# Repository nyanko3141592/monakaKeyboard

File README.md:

# monakaKeyboard

monakaKeyboard は、自作キーボードのプロジェクトです。このリポジトリには、キーボードの設計ファイル、ファームウェア、キーキャップデザイン、ケースの 3D モデルなどが含まれています。

## プロジェクト構成

```
.
├── 3DModel
│   ├── Case
│   │   ├── bottomboard.stl
│   │   └── topboard.stl
│   └── keycap
│       ├── alphabet_keycap.stl
│       └── symbol_keycap.stl
├── 3x7
├── README.md
└── choco002
    ├── keyboard.json
    ├── keymaps
    │   └── default
    │       └── keymap.c
    └── readme.md
```

### 3DModel

- `Case/`  
  ケースの 3D モデルが含まれています。

  - `bottomboard.stl` - 底板の 3D モデル
  - `topboard.stl` - 上部パネルの 3D モデル

- `keycap/`  
  キーキャップの 3D モデルが含まれています。
  - `alphabet_keycap.stl` - アルファベットキー用キーキャップ
  - `symbol_keycap.stl` - シンボルキー用キーキャップ

### 3x7

3x7 キー配列の設計データが含まれています。
3x7/DisliKey.kicad_pro から kicad で開いて Gerber ファイルを発注することができます。

### choco002

QMK ファームウェアの設定ファイルが含まれています。

- `keyboard.json`  
  キーボードの設定ファイルです。

- `keymaps/`  
  キーマップの定義が含まれています。
  - `default/keymap.c` - デフォルトのキーマップ定義

## 使い方

### 3D モデルの印刷

`3DModel`ディレクトリ内の STL ファイルを 3D プリンターで印刷してください。ケースとキーキャップを含めた全ての部品を印刷することで、物理的なキーボードを組み立てることができます。

### QMK ファームウェアの設定

`choco002`ディレクトリ内のファイルを使用して、QMK ファームウェアをビルドおよびフラッシュします。キーマップはデフォルト設定で使用できますが、`keymap.c`ファイルを編集することでカスタマイズが可能です。

1. QMK CLI をインストールしていない場合は[こちら](https://docs.qmk.fm/#/ja/getting_started_build_tools)からインストールしてください。
2. `choco002`ディレクトリに移動し、次のコマンドを実行します。

   ```
   qmk compile -kb choco002 -km default
   qmk flash -kb choco002 -km default
   ```

## ライセンス

このプロジェクトは、商用利用を除く目的での使用、改変、および出力を許可します。

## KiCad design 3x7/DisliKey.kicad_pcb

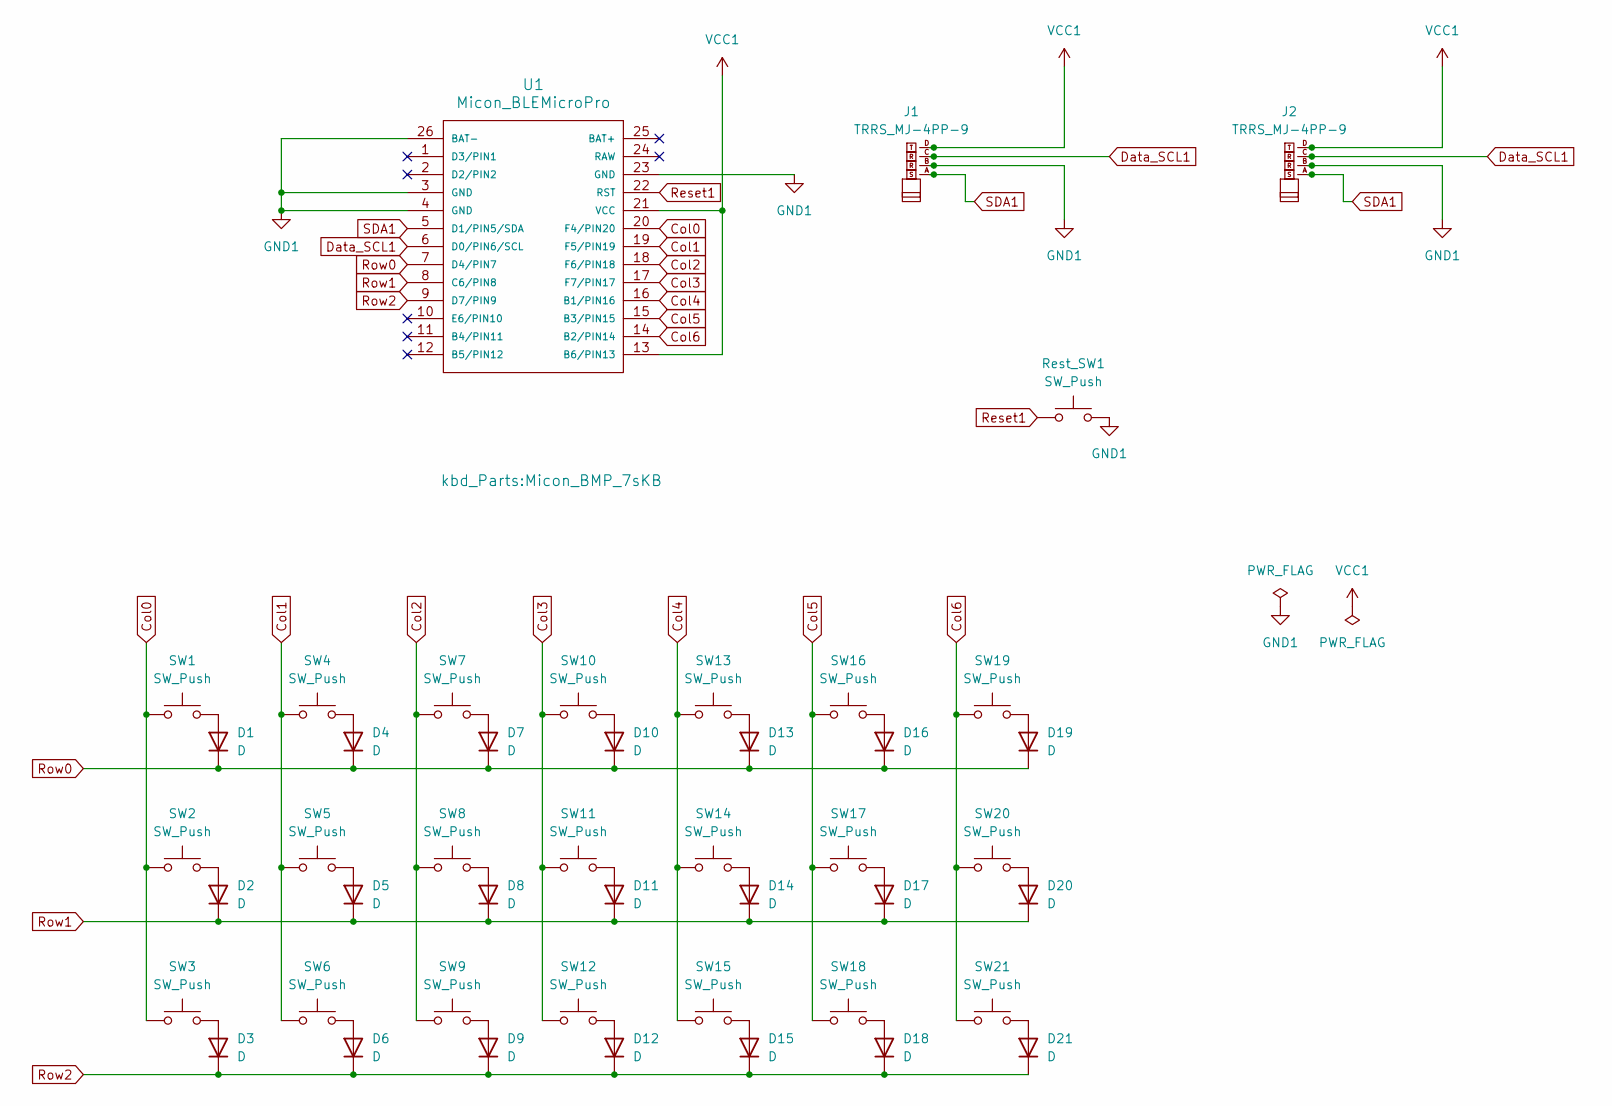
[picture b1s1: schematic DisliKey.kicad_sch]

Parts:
D1, D2, D3, D4, D5, D6, D7, D8, D9, D10, D11, D12, D13, D14, D15, D16, D17, D18, D19, D20, D21: D; Diode_TH
J1, J2: TRRS_MJ-4PP-9
Rest_SW1: SW_Push; ResetSW
SW1, SW2, SW3, SW4, SW5, SW6, SW7, SW8, SW9, SW10, SW11, SW12, SW13, SW14, SW15, SW16, SW17, SW18, SW19, SW20, SW21: SW_Push; CherryMX_Solder_1u
U1: Micon_BLEMicroPro; Micon_BMP_7sKB

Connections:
Col0: SW1.1, SW2.1, SW3.1, U1.20 (F4/PIN20)
Col1: SW4.1, SW5.1, SW6.1, U1.19 (F5/PIN19)
Col2: SW7.1, SW8.1, SW9.1, U1.18 (F6/PIN18)
Col3: SW10.1, SW11.1, SW12.1, U1.17 (F7/PIN17)
Col4: SW13.1, SW14.1, SW15.1, U1.16 (B1/PIN16)
Col5: SW16.1, SW17.1, SW18.1, U1.15 (B3/PIN15)
Col6: SW19.1, SW20.1, SW21.1, U1.14 (B2/PIN14)
Data_SCL1: J1.C, J2.C, U1.6 (D0/PIN6/SCL)
GND1: J1.B, J2.B, Rest_SW1.2, U1.3 (GND), U1.4 (GND), U1.23 (GND), U1.26 (BAT-)
unnamed: D1.2 (A), SW1.2
unnamed: D2.2 (A), SW2.2
unnamed: D3.2 (A), SW3.2
unnamed: D4.2 (A), SW4.2
unnamed: D5.2 (A), SW5.2
unnamed: D6.2 (A), SW6.2
unnamed: D7.2 (A), SW7.2
unnamed: D8.2 (A), SW8.2
unnamed: D9.2 (A), SW9.2
unnamed: D10.2 (A), SW10.2
unnamed: D11.2 (A), SW11.2
unnamed: D12.2 (A), SW12.2
unnamed: D13.2 (A), SW13.2
unnamed: D14.2 (A), SW14.2
unnamed: D15.2 (A), SW15.2
unnamed: D16.2 (A), SW16.2
unnamed: D17.2 (A), SW17.2
unnamed: D18.2 (A), SW18.2
unnamed: D19.2 (A), SW19.2
unnamed: D20.2 (A), SW20.2
unnamed: D21.2 (A), SW21.2
Reset1: Rest_SW1.1, U1.22 (RST)
Row0: D1.1 (K), D4.1 (K), D7.1 (K), D10.1 (K), D13.1 (K), D16.1 (K), D19.1 (K), U1.7 (D4/PIN7)
Row1: D2.1 (K), D5.1 (K), D8.1 (K), D11.1 (K), D14.1 (K), D17.1 (K), D20.1 (K), U1.8 (C6/PIN8)
Row2: D3.1 (K), D6.1 (K), D9.1 (K), D12.1 (K), D15.1 (K), D18.1 (K), D21.1 (K), U1.9 (D7/PIN9)
SDA1: J1.A, J2.A, U1.5 (D1/PIN5/SDA)
VCC1: J1.D, J2.D, U1.13 (B6/PIN13), U1.21 (VCC)

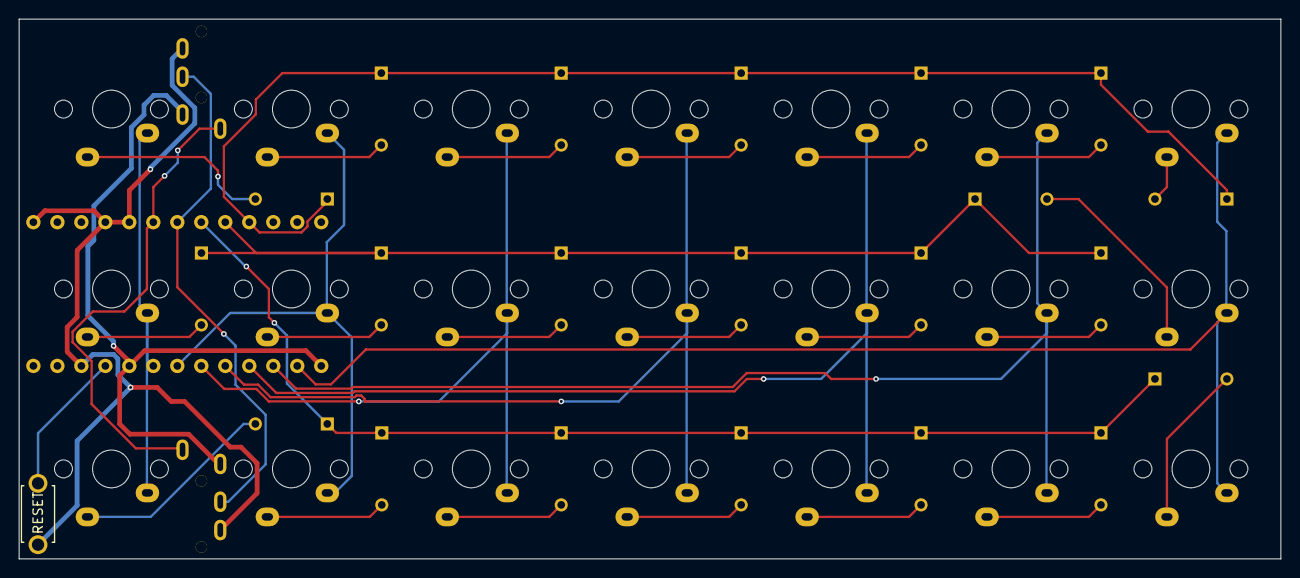
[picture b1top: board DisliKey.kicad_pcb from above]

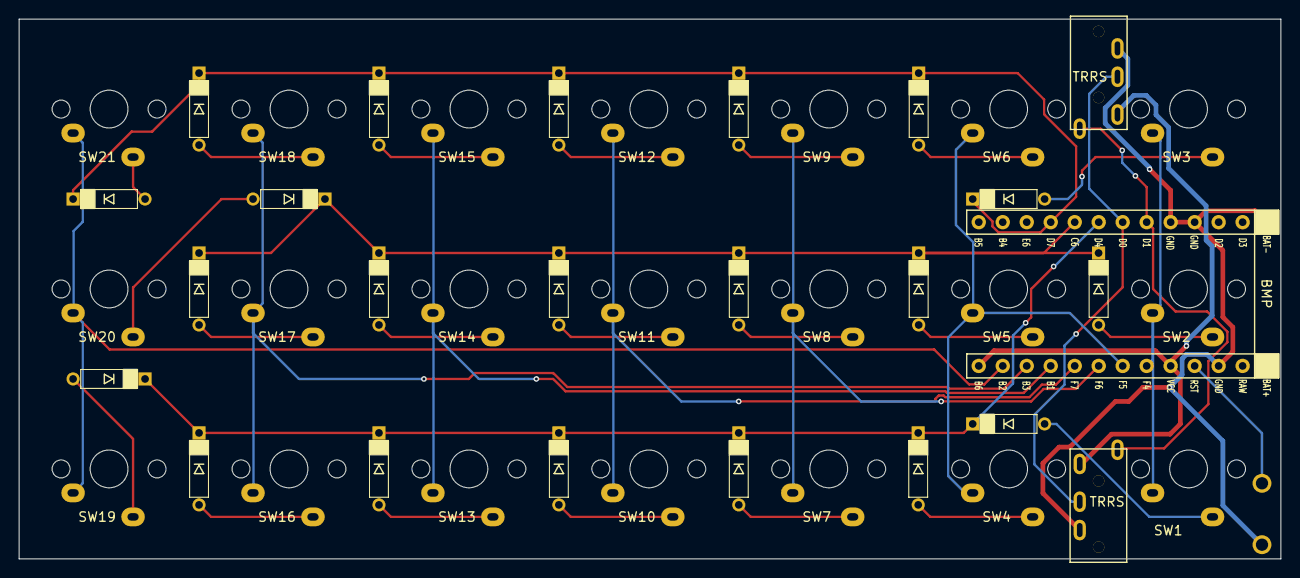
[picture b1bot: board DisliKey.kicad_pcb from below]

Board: 2 copper layers, 133.6 x 57.2 mm, 46 parts (2 on the bottom side), 36 nets.
